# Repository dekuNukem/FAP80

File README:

This repo is still under construction, more information will be available as I continue to add to the documentations and clean up the codebase...

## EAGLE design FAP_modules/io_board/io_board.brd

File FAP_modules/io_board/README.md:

FAP80 I/O Board

This is the I/O board that takes care of Z80 port I/O and interrupts. An EPM570 CPLD replaces 2 dozens of 74 series chips, and a STM32F051C8T6 take on the role of Port and Interrupt controller.

## Overview

* EPM570 CPLD glue logic
* STM32 IO/interrupt controller
* all interrupt modes supported
* 16 ports
* RTC
* UARTs
* Timers
* SD card
* I2C EEPROM
* PS/2 Keyboard
* ESP8266 Header

## Design details

Please see this detailed write-up about the design of this board: [click here](https://dekunukem.wordpress.com/2016/12/25/fap-rebord-the-new-io-card/)

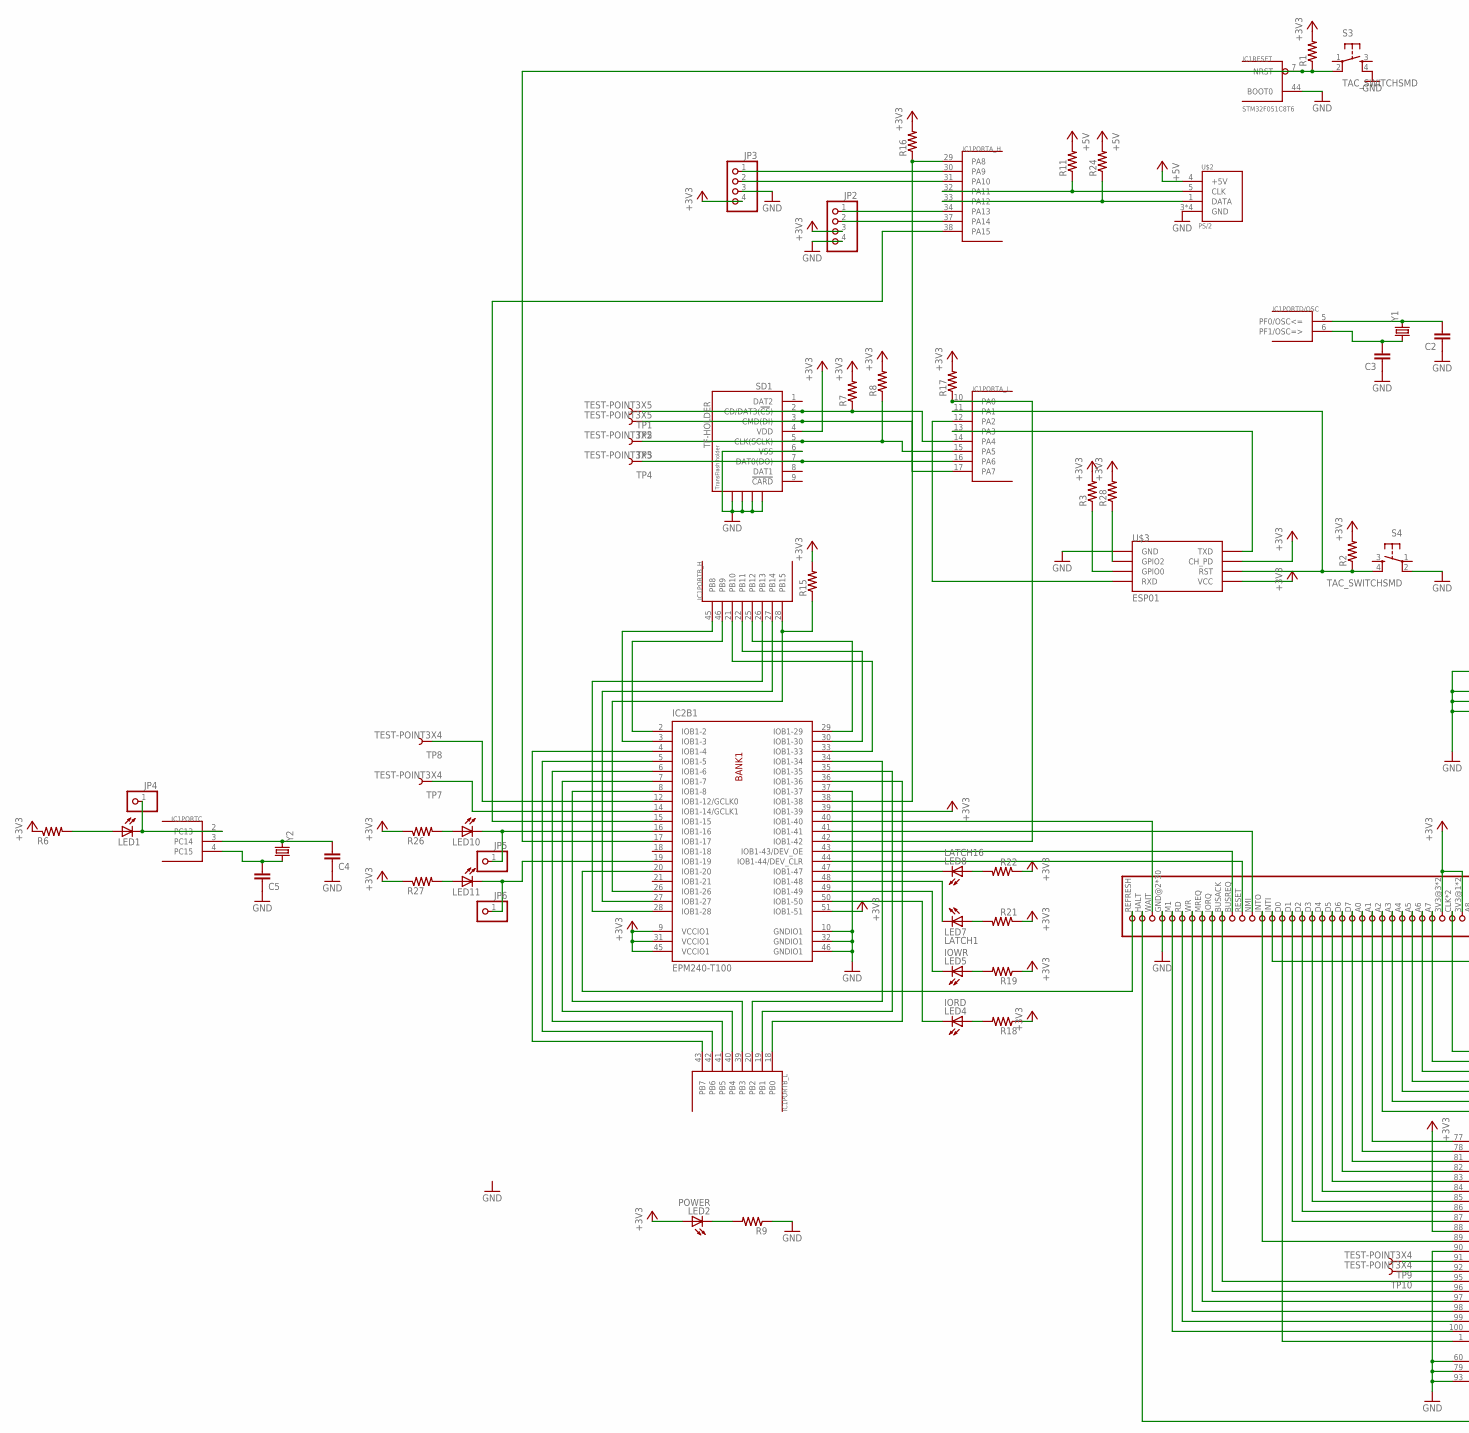
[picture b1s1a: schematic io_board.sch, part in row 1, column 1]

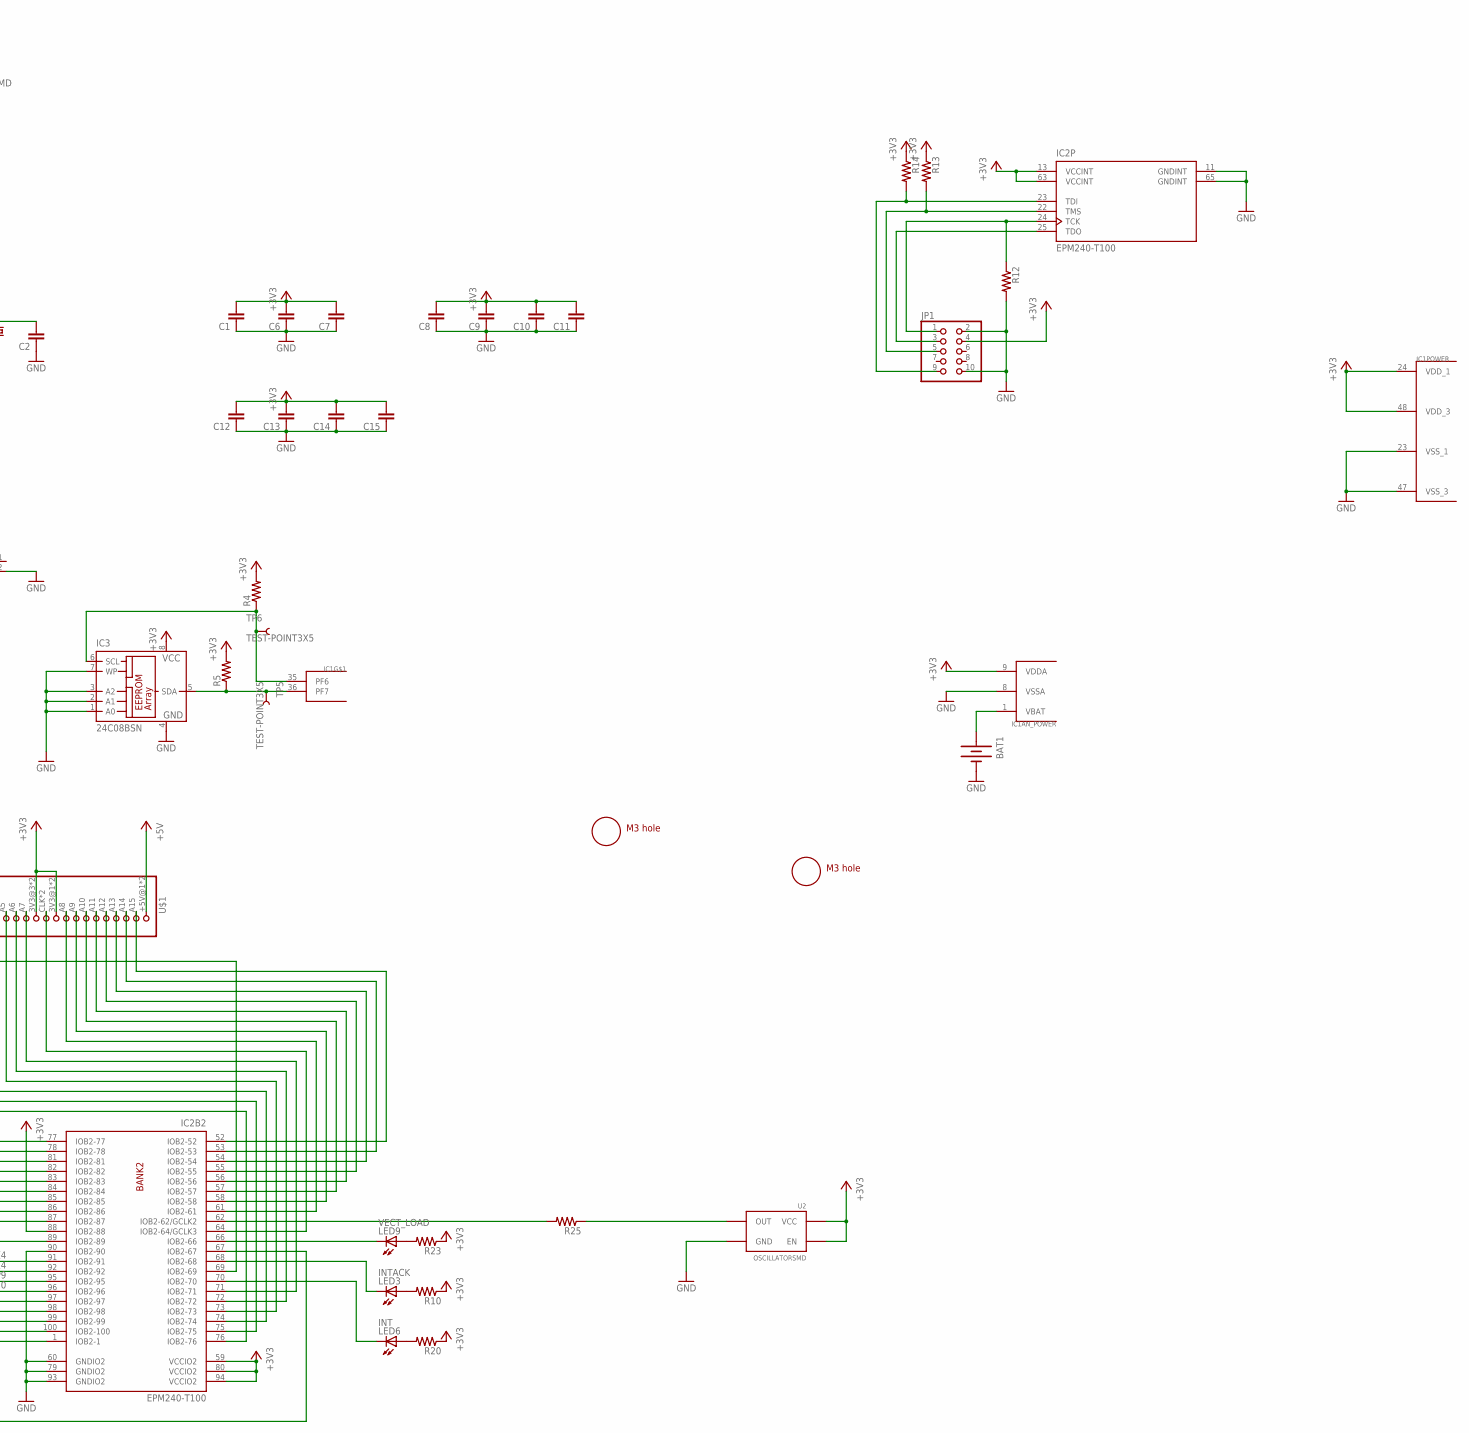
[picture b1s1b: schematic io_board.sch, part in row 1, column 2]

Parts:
BAT1: BATTERY20PTH; BATTCOM_20MM_PTH
C1, C2, C3, C4, C5, C6, C7, C8, C9, C10, C11, C12, C13, C14, C15: CAP0805; 0805
IC1: STM32F051C8T6; TQFP48
IC2: EPM240-T100; TQFP100
IC3: 24C08BSN; SO-08
JP1: PINHD-2X5; 2X05
JP2, JP3: PINHD-1X4/90; 1X04/90
JP4, JP5, JP6: PINHD-1X1; 1X01
LED1, LED10, LED11: LEDCHIP-LED0805; CHIP-LED0805
LED2: POWER; CHIPLED_0805
LED3: INTACK; CHIP-LED0805
LED4: IORD; CHIP-LED0805
LED5: IOWR; CHIP-LED0805
LED6: INT; CHIP-LED0805
LED7: LATCH1; CHIP-LED0805
LED8: LATCH16; CHIP-LED0805
LED9: VECT_LOAD; CHIP-LED0805
R1, R2, R3, R4, R5, R6, R7, R8, R9, R10, R11, R12, R13, R14, R15, R16, R17, R18, R19, R20, R21, R22, R23, R24, R25, R26, R27, R28: RESISTOR0805-RES; 0805
S3, S4: TAC_SWITCHSMD; TACTILE-SWITCH-SMD
SD1: TF-HOLDER; TF-PULL
TP1, TP2, TP3, TP4, TP5, TP6: TEST-POINT3X5; PAD.03X.05
TP7, TP8, TP9, TP10: TEST-POINT3X4; PAD.03X.04
U2: OSCILLATORSMD; CRYSTAL-SMD-7X5
U$1: FAP_BUS; 2X38
U$2: PS/2
U$3: ESP01
U$4, U$5: M3_MOUNTING_HOLE; M3_MOUNTING_HOLE_PACK
Y1: CRYSTALHC49US; HC49US
Y2: CRYSTALTC26H_EZ; TC26HEZ

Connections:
+3V3: C1.2, C6.2, C7.2, C8.2, C9.2, C10.2, C11.2, C12.2, C13.2, C14.2, C15.2, IC1.9 (VDDA), IC1.24 (VDD_1), IC1.48 (VDD_3), IC2.9 (VCCIO1), IC2.13 (VCCINT), IC2.31 (VCCIO1), IC2.39 (IOB1-39), IC2.45 (VCCIO1), IC2.51 (IOB1-51), IC2.59 (VCCIO2), IC2.63 (VCCINT), IC2.80 (VCCIO2), IC2.88 (IOB2-88), IC2.94 (VCCIO2), IC3.8 (VCC), JP1.4, JP2.3, JP3.4, LED2.A, R1.2, R2.2, R3.2, R4.2, R5.2, R6.1, R7.2, R8.2, R10.1, R13.1, R14.1, R15.2, R16.2, R17.2, R18.1, R19.1, R20.1, R21.1, R22.1, R23.1, R26.1, R27.1, R28.2, SD1.4 (VDD), U2.P$1 (EN), U2.P$4 (VCC), U$1.3V3@1 (10), U$1.3V3@2 (10), U$1.3V3@3 (12), U$1.3V3@4 (12), U$3.CH_PD, U$3.VCC
+5V: R11.2, R24.2, U$1.+5V@1 (1), U$1.+5V@2 (1), U$2.4 (+5V)
GND: BAT1.2 (-), C1.1, C2.1, C3.1, C4.1, C5.1, C6.1, C7.1, C8.1, C9.1, C10.1, C11.1, C12.1, C13.1, C14.1, C15.1, IC1.8 (VSSA), IC1.23 (VSS_1), IC1.44 (BOOT0), IC1.47 (VSS_3), IC2.10 (GNDIO1), IC2.11 (GNDINT), IC2.32 (GNDIO1), IC2.37 (IOB1-37), IC2.46 (GNDIO1), IC2.60 (GNDIO2), IC2.65 (GNDINT), IC2.79 (GNDIO2), IC2.90 (IOB2-90), IC2.93 (GNDIO2), IC3.1 (A0), IC3.2 (A1), IC3.3 (A2), IC3.4 (GND), IC3.7 (WP), JP1.2, JP1.10, JP2.4, JP3.3, R9.1, R12.2, S3.4, S4.2, SD1.6 (VSS), SD1.S1, SD1.S2, SD1.S3, SD1.S4, U2.P$2 (GND), U$1.GND@2 (GND), U$1.GND@3 (GND), U$1.GND@4 (GND), U$1.GND@5 (GND), U$1.GND@6 (GND), U$1.GND@7 (GND), U$1.GND@8 (GND), U$1.GND@9 (GND), U$1.GND@13 (GND), U$1.GND@14 (GND), U$1.GND@15 (GND), U$1.GND@16 (GND), U$1.GND@17 (GND), U$1.GND@18 (GND), U$1.GND@19 (GND), U$1.GND@20 (GND), U$1.GND@21 (GND), U$1.GND@22 (GND), U$1.GND@23 (GND), U$1.GND@24 (GND), U$1.GND@25 (GND), U$1.GND@26 (GND), U$1.GND@27 (GND), U$1.GND@28 (GND), U$1.GND@30 (GND), U$1.GND@34 (GND), U$1.GND@35 (GND), U$1.GND@36 (GND), U$1.GND@37 (GND), U$1.GND@38 (GND), U$2.3 (GND), U$2.P$1 (GND), U$2.P$2 (GND), U$2.P$3 (GND), U$3.GND
unnamed: IC2.67 (IOB2-67), U$1.HALT (41)
unnamed: R25.1, U2.P$3 (OUT)
unnamed: IC2.20 (IOB1-20), U$1.REFRESH (42)
unnamed: IC2.12 (IOB1-12/GCLK0), TP8.P$1
unnamed: IC1.7 (NRST), IC2.17 (IOB1-17), R1.1, S3.2
unnamed: C2.2, IC1.5 (PF0/OSC<=), Y1.2
unnamed: C3.2, IC1.6 (PF1/OSC=>), Y1.1
unnamed: C4.2, IC1.3 (PC14), Y2.2
unnamed: C5.2, IC1.4 (PC15), Y2.1
unnamed: BAT1.1 (+), IC1.1 (VBAT)
unnamed: IC1.37 (PA14), JP2.2
unnamed: IC1.34 (PA13), JP2.1
unnamed: IC2.62 (IOB2-62/GCLK2), R25.2
unnamed: IC2.43 (IOB1-43/DEV_OE), U$1.BUSREQ (32)
unnamed: IC2.100 (IOB2-100), U$1.M1 (38)
unnamed: IC2.99 (IOB2-99), U$1.RD (37)
unnamed: IC2.98 (IOB2-98), U$1.WR (36)
unnamed: IC2.97 (IOB2-97), U$1.MREQ (35)
unnamed: IC2.96 (IOB2-96), U$1.IORQ (34)
unnamed: IC2.95 (IOB2-95), U$1.BUSACK (33)
unnamed: IC2.44 (IOB1-44/DEV_CLR), U$1.RESET (31)
unnamed: LED3.A, R10.2
unnamed: IC2.89 (IOB2-89), U$1.INTO (39)
unnamed: IC2.1 (IOB2-1), U$1.D0 (28)
unnamed: IC2.87 (IOB2-87), U$1.D1 (27)
unnamed: IC2.86 (IOB2-86), U$1.D2 (26)
unnamed: IC2.85 (IOB2-85), U$1.D3 (25)
unnamed: IC2.84 (IOB2-84), U$1.D4 (24)
unnamed: IC2.83 (IOB2-83), U$1.D5 (23)
unnamed: IC2.82 (IOB2-82), U$1.D6 (22)
unnamed: IC2.81 (IOB2-81), U$1.D7 (21)
unnamed: IC2.78 (IOB2-78), U$1.A0 (20)
unnamed: IC2.77 (IOB2-77), U$1.A1 (19)
unnamed: IC2.76 (IOB2-76), U$1.A2 (18)
unnamed: IC2.75 (IOB2-75), U$1.A3 (17)
unnamed: IC2.74 (IOB2-74), U$1.A4 (16)
unnamed: IC2.73 (IOB2-73), U$1.A5 (15)
unnamed: IC2.72 (IOB2-72), U$1.A6 (14)
unnamed: IC2.71 (IOB2-71), U$1.A7 (13)
unnamed: IC2.64 (IOB2-64/GCLK3), U$1.CLK (11), U$1.CLK@2 (11)
unnamed: IC2.61 (IOB2-61), U$1.A8 (9)
unnamed: IC2.58 (IOB2-58), U$1.A9 (8)
unnamed: IC2.57 (IOB2-57), U$1.A10 (7)
unnamed: IC2.56 (IOB2-56), U$1.A11 (6)
unnamed: IC2.55 (IOB2-55), U$1.A12 (5)
unnamed: IC2.54 (IOB2-54), U$1.A13 (4)
unnamed: IC2.53 (IOB2-53), U$1.A14 (3)
unnamed: IC2.52 (IOB2-52), U$1.A15 (2)
unnamed: IC1.46 (PB9), IC2.2 (IOB1-2)
unnamed: IC1.45 (PB8), IC2.3 (IOB1-3)
unnamed: IC1.43 (PB7), IC2.4 (IOB1-4)
unnamed: IC1.42 (PB6), IC2.5 (IOB1-5)
unnamed: IC1.41 (PB5), IC2.6 (IOB1-6)
unnamed: IC1.40 (PB4), IC2.7 (IOB1-7)
unnamed: IC1.39 (PB3), IC2.8 (IOB1-8)
unnamed: IC1.28 (PB15), IC2.26 (IOB1-26), R15.1
unnamed: IC1.27 (PB14), IC2.27 (IOB1-27)
unnamed: IC1.26 (PB13), IC2.28 (IOB1-28)
unnamed: IC1.25 (PB12), IC2.29 (IOB1-29)
unnamed: IC1.22 (PB11), IC2.30 (IOB1-30)
unnamed: IC1.21 (PB10), IC2.33 (IOB1-33)
unnamed: IC1.20 (PB2), IC2.34 (IOB1-34)
unnamed: IC1.19 (PB1), IC2.35 (IOB1-35)
unnamed: IC1.18 (PB0), IC2.36 (IOB1-36)
unnamed: IC1.32 (PA11), R11.1, U$2.5 (CLK)
unnamed: IC1.33 (PA12), R24.1, U$2.1 (DATA)
unnamed: IC1.11 (PA1), R2.1, S4.4, U$3.RST
unnamed: R3.1, U$3.GPIO0
unnamed: IC1.36 (PF7), IC3.5 (SDA), R5.1, TP5.P$1
unnamed: IC1.35 (PF6), IC3.6 (SCL), R4.1, TP6.P$1
unnamed: IC1.31 (PA10), JP3.2
unnamed: IC1.30 (PA9), JP3.1
unnamed: IC1.2 (PC13), JP4.1, LED1.C
unnamed: LED1.A, R6.2
unnamed: IC1.12 (PA2), U$3.RX (RXD)
unnamed: IC1.13 (PA3), U$3.TX (TXD)
unnamed: LED4.A, R18.2
unnamed: IC1.14 (PA4), R7.1, SD1.2 (CD/DAT3(!CS!)), TP1.P$1
unnamed: IC1.17 (PA7), SD1.3 (CMD(DI)), TP2.P$1
unnamed: IC1.16 (PA6), SD1.7 (DAT0(DO)), TP4.P$1
unnamed: IC1.15 (PA5), R8.1, SD1.5 (CLK(SCLK)), TP3.P$1
unnamed: LED2.C, R9.2
unnamed: LED7.A, R21.2
unnamed: LED5.A, R19.2
unnamed: IC1.38 (PA15), IC2.15 (IOB1-15)
unnamed: IC1.10 (PA0), IC2.42 (IOB1-42), R17.1
unnamed: IC1.29 (PA8), IC2.38 (IOB1-38), R16.1
unnamed: LED6.A, R20.2
unnamed: LED8.A, R22.2
unnamed: IC2.47 (IOB1-47), LED8.C
unnamed: IC2.48 (IOB1-48), LED7.C
unnamed: IC2.49 (IOB1-49), LED5.C
unnamed: IC2.50 (IOB1-50), LED4.C
unnamed: LED9.A, R23.2
unnamed: IC2.66 (IOB2-66), LED9.C
unnamed: IC2.68 (IOB2-68), LED3.C
unnamed: IC2.70 (IOB2-70), LED6.C
unnamed: IC2.14 (IOB1-14/GCLK1), TP7.P$1
unnamed: IC2.69 (IOB2-69), U$1.INTI (29)
unnamed: IC2.41 (IOB1-41), U$1.NMI (30)
unnamed: IC2.40 (IOB1-40), U$1.WAIT (40)
unnamed: LED10.A, R26.2
unnamed: IC2.16 (IOB1-16), JP5.1, LED10.C
unnamed: LED11.A, R27.2
unnamed: IC2.19 (IOB1-19), JP6.1, LED11.C
unnamed: IC2.91 (IOB2-91), TP9.P$1
unnamed: IC2.92 (IOB2-92), TP10.P$1
unnamed: R28.1, U$3.GPIO2
TCK: IC2.24 (TCK), JP1.1, R12.1
TDI: IC2.23 (TDI), JP1.9, R14.2
TDO: IC2.25 (TDO), JP1.3
TMS: IC2.22 (TMS), JP1.5, R13.2

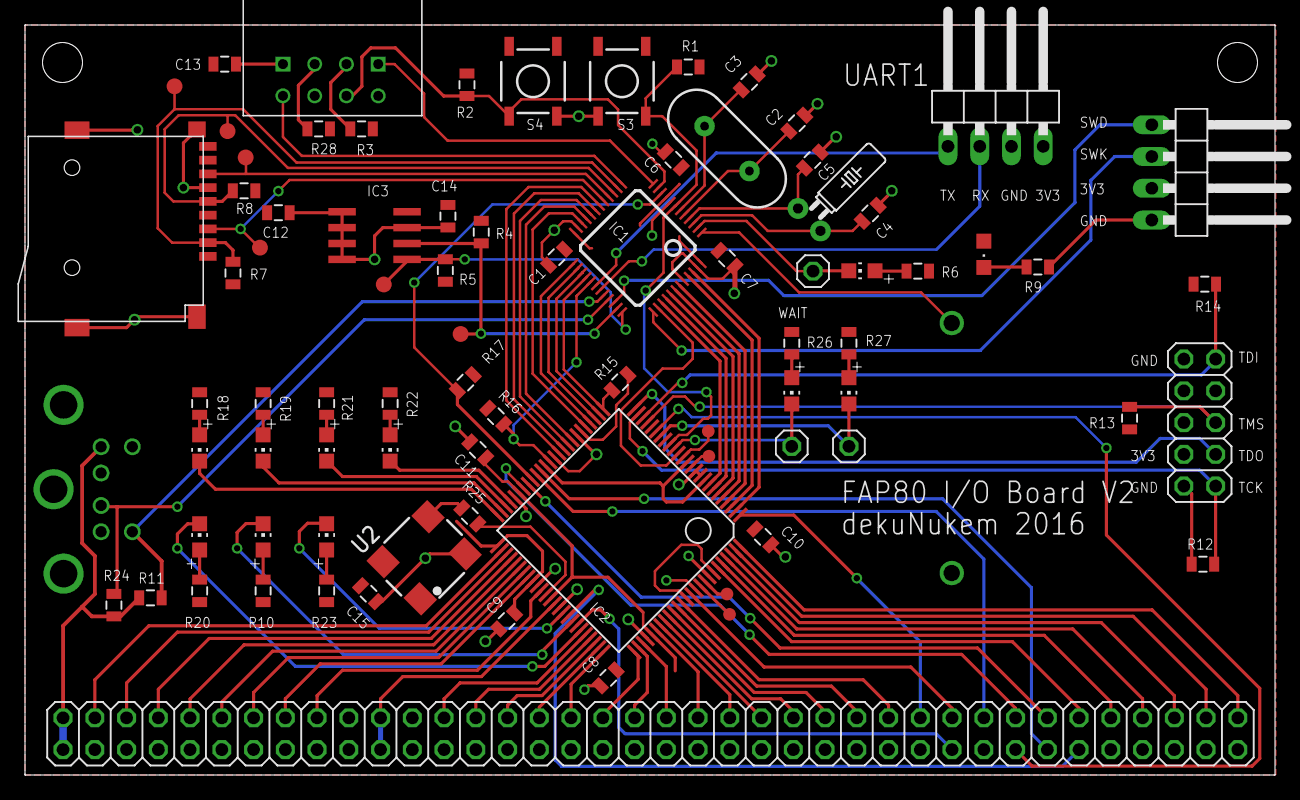
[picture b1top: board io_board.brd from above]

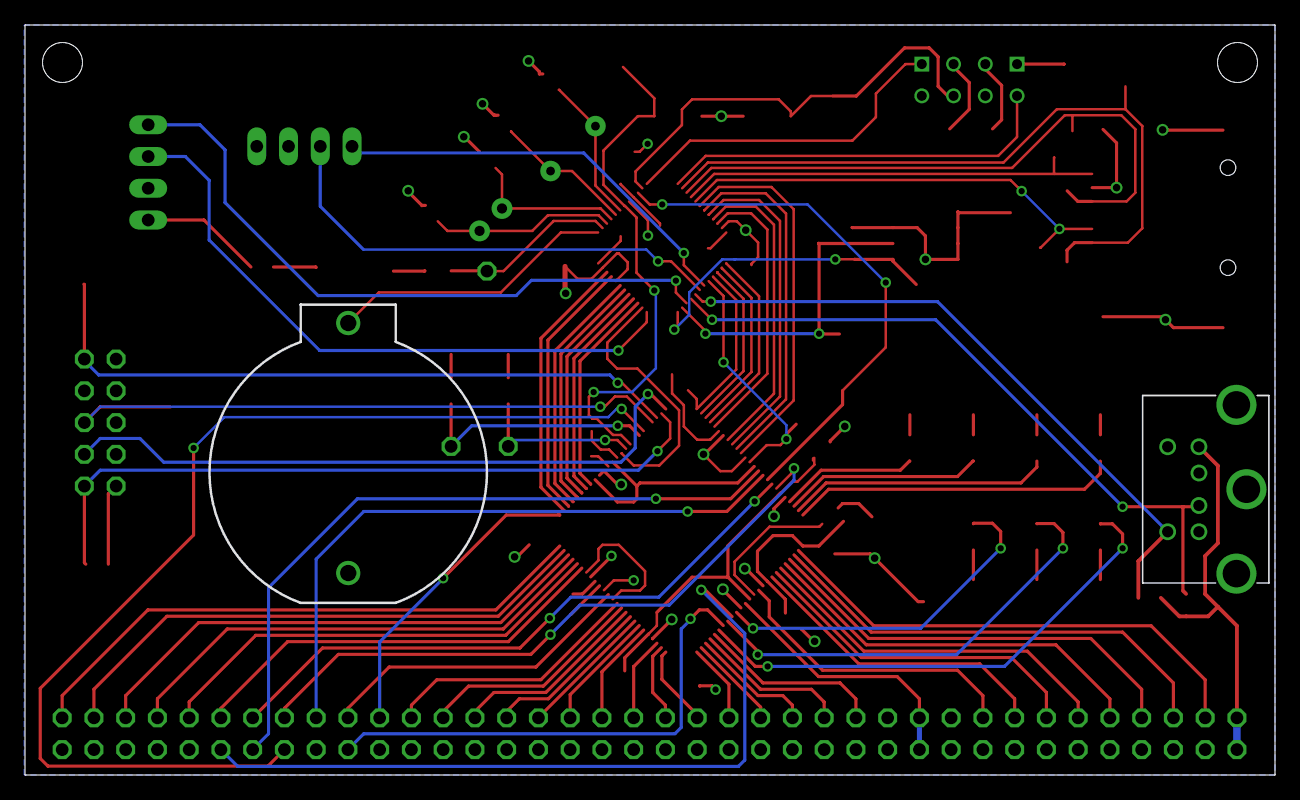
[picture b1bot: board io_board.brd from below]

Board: 2 copper layers, 100.0 x 60.0 mm, 85 parts (2 on the bottom side), 115 nets.

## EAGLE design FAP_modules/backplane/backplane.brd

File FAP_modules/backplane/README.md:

# FAP80 active backplane

The backbone of FAP80, all the modules plug into it. The backplane has 5 slots, each 2cm apart, a STM32F072RBT6, a 2.2 inch serial LCD for displaying execution status, and 6 buttons for controlling the computer.

The entire bus is connected to the STM32, which drives the Z80 clock through one of its PWM channels, the uC also monitors the bus content and display it on a LCD. It can also kick the Z80 off the bus and read/write ROM/RAM directly. The backplane communicates with a PC via USB, which also powers the FAP80.

## Usage

When powered on, the backplane resets the Z80 then stops. Press RUN/STOP button to start FAP80 execution at full speed, press CLK STEP for single clock step, press INS STEP for single instruction step(which takes variable numbers of clock cycles depending on the instruction), press Z80 RESET to reset the Z80, and MCU RESET to reset the backplane itself. TRACE button currently doesn't do anything, I'll implement trace function when I need it.

The backplane will appear as a USB serial device when plugged into a computer. send `epm` to enter program mode. Once entered, you can send `r address` to read a memory address, `w address value` to write to a memory address, and `z` to erase entire ROM to 0xff. Send `qpm` to quit program mode. Note all numerical arguments are in decimal, and all commands ends in `\r\n`.

## Bus connector

Each connector is a 38x2 double row female pin header, pinout below.
I used 2 rows to give more grip to modules that has been plugged in, as well as improving noise immunity.  All Z80 signals are available on the bus.

Interrupt chaining is supported. INTI is the interrupt input, while INTO is interrupt output. The board closest to the Z80 CPU board has the highest interrupt priority.

|     |        | 
|-----|--------| 
| GND | M1     | 
| GND | RD     | 
| GND | WR     | 
| GND | MREQ   | 
| GND | IORQ   | 
| HALT | BUACK  | 
| WAIT | BUSREQ | 
| REFRESH | RESET  | 
| GND | NMI    | 
| INTI | INTO    | 
| GND | D0     | 
| GND | D1     | 
| GND | D2     | 
| GND | D3     | 
| GND | D4     | 
| GND | D5     | 
| GND | D6     | 
| GND | D7     | 
| GND | A0     | 
| GND | A1     | 
| GND | A2     | 
| GND | A3     | 
| GND | A4     | 
| GND | A5     | 
| GND | A6     | 
| GND | A7     | 
| 3V3 | 3V3    | 
| CLK | CLK    | 
| 3V3 | 3V3    | 
| GND | A8     | 
| GND | A9     | 
| GND | A10    | 
| GND | A11    | 
| GND | A12    | 
| GND | A13    | 
| GND | A14    | 
| GND | A15    | 
| 5V  | 5V     | 

## LCD

I used a LCD from [Nextion](https://www.itead.cc/wiki/Nextion_HMI_Solution), they make a whole range of LCDs in different sizes, some with resistive touch screen. The neat thing is that they are controlled by standard serial, so it's much easier to use than I2C or SPI LCDs. And apparently it has a companion software on PC where you can design an entire UI and upload it into the LCD. For this project I didn't bother with any of that since it just displays some text strings. I used their smallest and cheapest one. The serial commands for it can be found [here](https://www.itead.cc/wiki/Nextion_Instruction_Set), the only two I used is CLS (clear screen) and XSTR(print string).

## Blog entries

For details about the old backplane, see [here](https://dekunukem.wordpress.com/2016/02/21/part-1-bus-board-cpu-board-and-freerunning-fap/)

For a brief introduction of the new backplane, see [here](https://dekunukem.wordpress.com/2016/12/22/fap-reborn-backplane/)

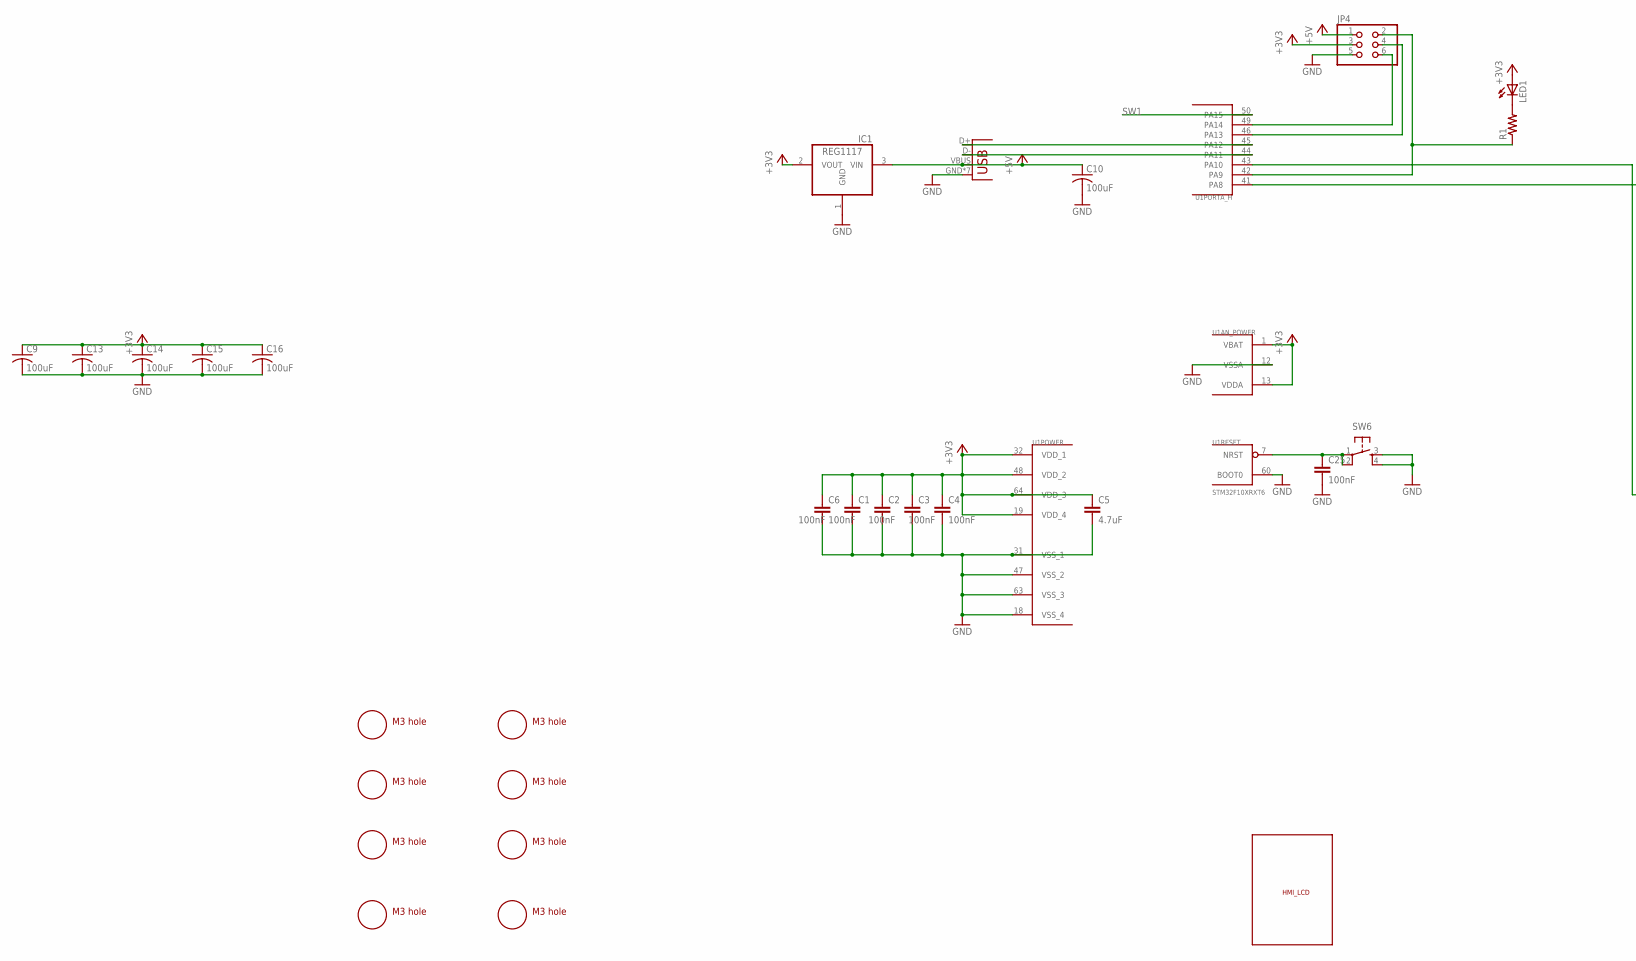
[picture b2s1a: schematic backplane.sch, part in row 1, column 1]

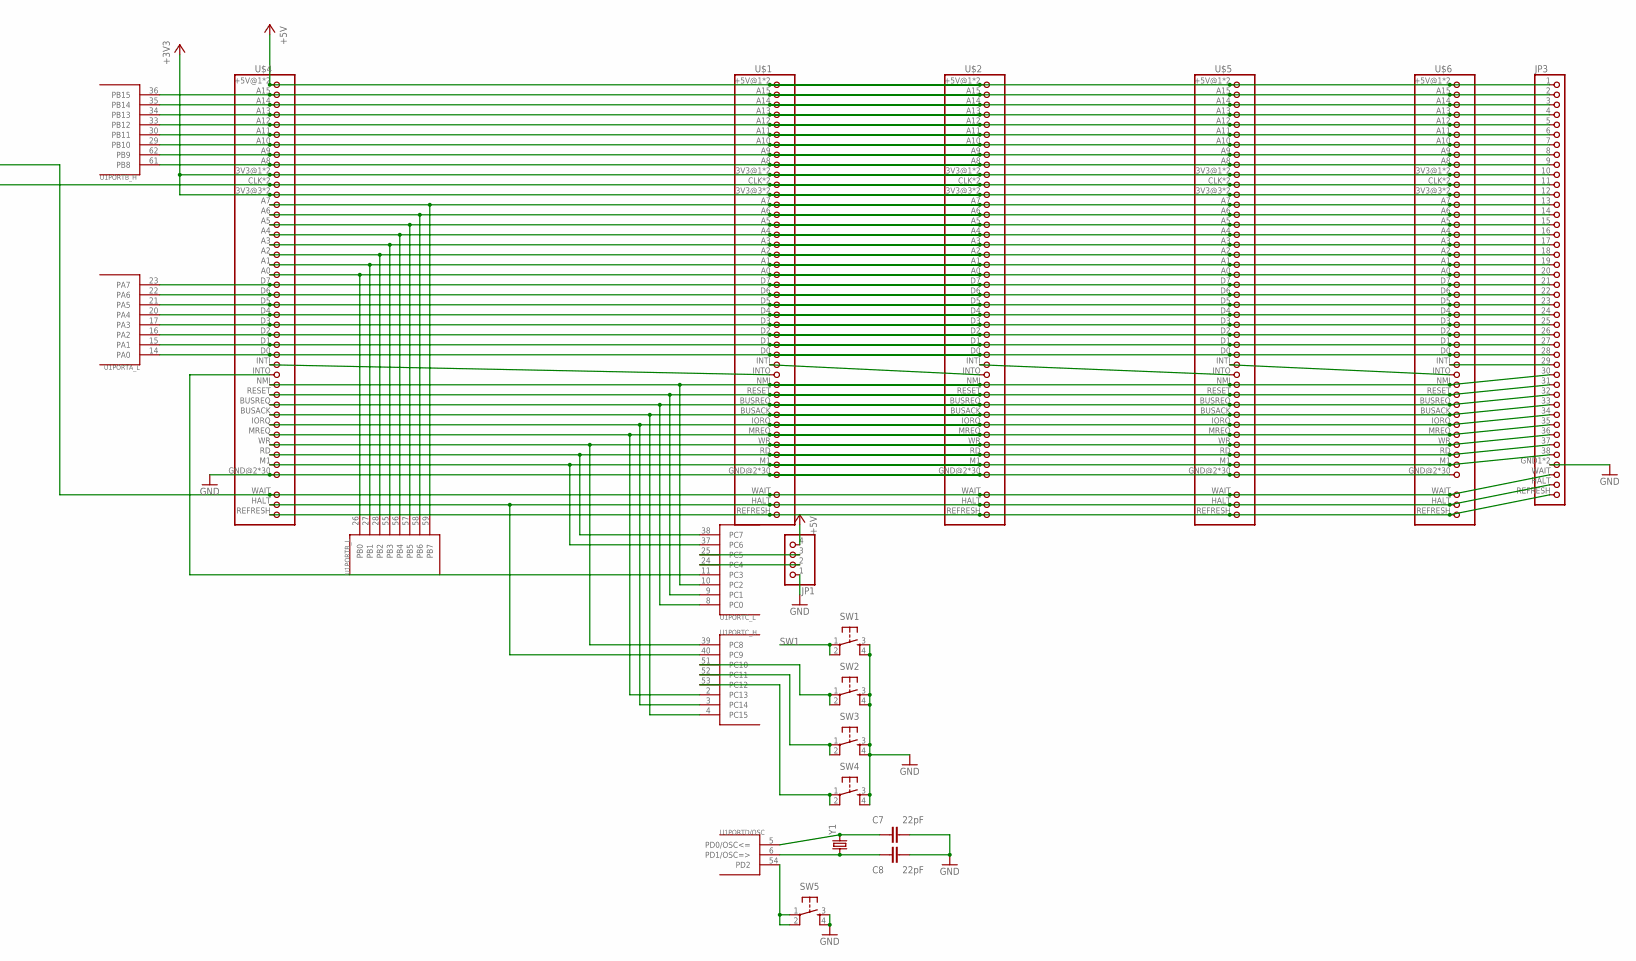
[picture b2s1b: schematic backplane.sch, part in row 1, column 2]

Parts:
C1, C2, C3, C4, C6, C25: 100nF; 0805
C5: 4.7uF; 0805
C7, C8: 22pF; 0805
C9, C10, C13, C14, C15, C16: 100uF; C1210
IC1: REG1117; SOT223
J1: USB-MICROB
JP1: PINHD-1X4; 1X04
JP3: PINHD-1X38; 1X38
JP4: PINHD-2X3; 2X03
LED1: LEDCHIP-LED0805; CHIP-LED0805
R1: R-US_R0805; R0805
SW1, SW2, SW3, SW4, SW5, SW6: SWITCH_SPST_4_PINSQUARE; TACTILE-SWITCH-SMD
U1: STM32F10XRXT6; TQFP64
U$1, U$2, U$4, U$5, U$6: FAP_BUS; 2X38
U$3: HMI_LCD
U$7, U$8, U$9, U$10, U$11, U$12, U$13, U$14: M3_MOUNTING_HOLE; M3_MOUNTING_HOLE_PACK
Y1: CRYSTALHC49US; HC49US

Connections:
+3V3: C1.1, C2.1, C3.1, C4.1, C5.1, C6.1, C9.1, C13.1, C14.1, C15.1, C16.1, IC1.2 (VOUT), JP3.10, JP3.12, JP4.3, LED1.A, U1.1 (VBAT), U1.13 (VDDA), U1.19 (VDD_4), U1.32 (VDD_1), U1.48 (VDD_2), U1.64 (VDD_3), U$1.3V3@1 (10), U$1.3V3@2 (10), U$1.3V3@3 (12), U$1.3V3@4 (12), U$2.3V3@1 (10), U$2.3V3@2 (10), U$2.3V3@3 (12), U$2.3V3@4 (12), U$4.3V3@1 (10), U$4.3V3@2 (10), U$4.3V3@3 (12), U$4.3V3@4 (12), U$5.3V3@1 (10), U$5.3V3@2 (10), U$5.3V3@3 (12), U$5.3V3@4 (12), U$6.3V3@1 (10), U$6.3V3@2 (10), U$6.3V3@3 (12), U$6.3V3@4 (12)
+5V: C10.1, IC1.3 (VIN), J1.VBUS, JP1.4, JP3.1, JP4.1, U$1.+5V@1 (1), U$1.+5V@2 (1), U$2.+5V@1 (1), U$2.+5V@2 (1), U$4.+5V@1 (1), U$4.+5V@2 (1), U$5.+5V@1 (1), U$5.+5V@2 (1), U$6.+5V@1 (1), U$6.+5V@2 (1)
A0: JP3.20, U1.26 (PB0), U$1.A0 (20), U$2.A0 (20), U$4.A0 (20), U$5.A0 (20), U$6.A0 (20)
A7: JP3.13, U1.59 (PB7), U$1.A7 (13), U$2.A7 (13), U$4.A7 (13), U$5.A7 (13), U$6.A7 (13)
GND: C1.2, C2.2, C3.2, C4.2, C5.2, C6.2, C7.2, C8.2, C9.2, C10.2, C13.2, C14.2, C15.2, C16.2, C25.2, IC1.1 (GND), J1.GND, J1.P1 (GND), J1.P2 (GND), J1.P3 (GND), J1.P4 (GND), J1.P5 (GND), J1.P6 (GND), JP1.1, JP3.GND1 (GND), JP3.GND2 (GND), JP4.5, SW1.3, SW1.4, SW2.3, SW2.4, SW3.3, SW3.4, SW4.3, SW4.4, SW5.3, SW5.4, SW6.3, SW6.4, U1.12 (VSSA), U1.18 (VSS_4), U1.31 (VSS_1), U1.47 (VSS_2), U1.60 (BOOT0), U1.63 (VSS_3), U$1.GND@2 (GND), U$1.GND@3 (GND), U$1.GND@4 (GND), U$1.GND@5 (GND), U$1.GND@6 (GND), U$1.GND@7 (GND), U$1.GND@8 (GND), U$1.GND@9 (GND), U$1.GND@13 (GND), U$1.GND@14 (GND), U$1.GND@15 (GND), U$1.GND@16 (GND), U$1.GND@17 (GND), U$1.GND@18 (GND), U$1.GND@19 (GND), U$1.GND@20 (GND), U$1.GND@21 (GND), U$1.GND@22 (GND), U$1.GND@23 (GND), U$1.GND@24 (GND), U$1.GND@25 (GND), U$1.GND@26 (GND), U$1.GND@27 (GND), U$1.GND@28 (GND), U$1.GND@30 (GND), U$1.GND@34 (GND), U$1.GND@35 (GND), U$1.GND@36 (GND), U$1.GND@37 (GND), U$1.GND@38 (GND), U$2.GND@2 (GND), U$2.GND@3 (GND), U$2.GND@4 (GND), U$2.GND@5 (GND), U$2.GND@6 (GND), U$2.GND@7 (GND), U$2.GND@8 (GND), U$2.GND@9 (GND), U$2.GND@13 (GND), U$2.GND@14 (GND), U$2.GND@15 (GND), U$2.GND@16 (GND), U$2.GND@17 (GND), U$2.GND@18 (GND), U$2.GND@19 (GND), U$2.GND@20 (GND), U$2.GND@21 (GND), U$2.GND@22 (GND), U$2.GND@23 (GND), U$2.GND@24 (GND), U$2.GND@25 (GND), U$2.GND@26 (GND), U$2.GND@27 (GND), U$2.GND@28 (GND), U$2.GND@30 (GND), U$2.GND@34 (GND), U$2.GND@35 (GND), U$2.GND@36 (GND), U$2.GND@37 (GND), U$2.GND@38 (GND), U$4.GND@2 (GND), U$4.GND@3 (GND), U$4.GND@4 (GND), U$4.GND@5 (GND), U$4.GND@6 (GND), U$4.GND@7 (GND), U$4.GND@8 (GND), U$4.GND@9 (GND), U$4.GND@13 (GND), U$4.GND@14 (GND), U$4.GND@15 (GND), U$4.GND@16 (GND), U$4.GND@17 (GND), U$4.GND@18 (GND), U$4.GND@19 (GND), U$4.GND@20 (GND), U$4.GND@21 (GND), U$4.GND@22 (GND), U$4.GND@23 (GND), U$4.GND@24 (GND), U$4.GND@25 (GND), U$4.GND@26 (GND), U$4.GND@27 (GND), U$4.GND@28 (GND), U$4.GND@30 (GND), U$4.GND@34 (GND), U$4.GND@35 (GND), U$4.GND@36 (GND), U$4.GND@37 (GND), U$4.GND@38 (GND), U$5.GND@2 (GND), U$5.GND@3 (GND), U$5.GND@4 (GND), U$5.GND@5 (GND), U$5.GND@6 (GND), U$5.GND@7 (GND), U$5.GND@8 (GND), U$5.GND@9 (GND), U$5.GND@13 (GND), U$5.GND@14 (GND), U$5.GND@15 (GND), U$5.GND@16 (GND), U$5.GND@17 (GND), U$5.GND@18 (GND), U$5.GND@19 (GND), U$5.GND@20 (GND), U$5.GND@21 (GND), U$5.GND@22 (GND), U$5.GND@23 (GND), U$5.GND@24 (GND), U$5.GND@25 (GND), U$5.GND@26 (GND), U$5.GND@27 (GND), U$5.GND@28 (GND), U$5.GND@30 (GND), U$5.GND@34 (GND), U$5.GND@35 (GND), U$5.GND@36 (GND), U$5.GND@37 (GND), U$5.GND@38 (GND), U$6.GND@2 (GND), U$6.GND@3 (GND), U$6.GND@4 (GND), U$6.GND@5 (GND), U$6.GND@6 (GND), U$6.GND@7 (GND), U$6.GND@8 (GND), U$6.GND@9 (GND), U$6.GND@13 (GND), U$6.GND@14 (GND), U$6.GND@15 (GND), U$6.GND@16 (GND), U$6.GND@17 (GND), U$6.GND@18 (GND), U$6.GND@19 (GND), U$6.GND@20 (GND), U$6.GND@21 (GND), U$6.GND@22 (GND), U$6.GND@23 (GND), U$6.GND@24 (GND), U$6.GND@25 (GND), U$6.GND@26 (GND), U$6.GND@27 (GND), U$6.GND@28 (GND), U$6.GND@30 (GND), U$6.GND@34 (GND), U$6.GND@35 (GND), U$6.GND@36 (GND), U$6.GND@37 (GND), U$6.GND@38 (GND)
unnamed: JP3.29, U$6.INTI (29)
unnamed: U$5.INTI (29), U$6.INTO (39)
unnamed: JP3.3, U1.35 (PB14), U$1.A14 (3), U$2.A14 (3), U$4.A14 (3), U$5.A14 (3), U$6.A14 (3)
unnamed: JP3.4, U1.34 (PB13), U$1.A13 (4), U$2.A13 (4), U$4.A13 (4), U$5.A13 (4), U$6.A13 (4)
unnamed: U$1.INTO (39), U$4.INTI (29)
unnamed: U$1.INTI (29), U$2.INTO (39)
unnamed: JP3.7, U1.29 (PB10), U$1.A10 (7), U$2.A10 (7), U$4.A10 (7), U$5.A10 (7), U$6.A10 (7)
unnamed: U1.11 (PC3), U$4.INTO (39)
unnamed: JP3.9, U1.61 (PB8), U$1.A8 (9), U$2.A8 (9), U$4.A8 (9), U$5.A8 (9), U$6.A8 (9)
unnamed: U$2.INTI (29), U$5.INTO (39)
unnamed: JP3.22, U1.22 (PA6), U$1.D6 (22), U$2.D6 (22), U$4.D6 (22), U$5.D6 (22), U$6.D6 (22)
unnamed: LED1.C, R1.2
unnamed: JP3.24, U1.20 (PA4), U$1.D4 (24), U$2.D4 (24), U$4.D4 (24), U$5.D4 (24), U$6.D4 (24)
unnamed: JP3.27, U1.15 (PA1), U$1.D1 (27), U$2.D1 (27), U$4.D1 (27), U$5.D1 (27), U$6.D1 (27)
unnamed: JP3.26, U1.16 (PA2), U$1.D2 (26), U$2.D2 (26), U$4.D2 (26), U$5.D2 (26), U$6.D2 (26)
unnamed: JP3.28, U1.14 (PA0), U$1.D0 (28), U$2.D0 (28), U$4.D0 (28), U$5.D0 (28), U$6.D0 (28)
unnamed: JP3.REFRESH, U$1.REFRESH, U$2.REFRESH, U$4.REFRESH, U$5.REFRESH, U$6.REFRESH
unnamed: JP3.30, U1.10 (PC2), U$1.NMI (30), U$2.NMI (30), U$4.NMI (30), U$5.NMI (30), U$6.NMI (30)
unnamed: JP3.HALT, U1.40 (PC9), U$1.HALT, U$2.HALT, U$4.HALT, U$5.HALT, U$6.HALT
unnamed: JP3.25, U1.17 (PA3), U$1.D3 (25), U$2.D3 (25), U$4.D3 (25), U$5.D3 (25), U$6.D3 (25)
unnamed: JP3.31, U1.9 (PC1), U$1.RESET (31), U$2.RESET (31), U$4.RESET (31), U$5.RESET (31), U$6.RESET (31)
unnamed: JP3.32, U1.8 (PC0), U$1.BUSREQ (32), U$2.BUSREQ (32), U$4.BUSREQ (32), U$5.BUSREQ (32), U$6.BUSREQ (32)
unnamed: JP3.35, U1.2 (PC13), U$1.MREQ (35), U$2.MREQ (35), U$4.MREQ (35), U$5.MREQ (35), U$6.MREQ (35)
unnamed: JP3.36, U1.39 (PC8), U$1.WR (36), U$2.WR (36), U$4.WR (36), U$5.WR (36), U$6.WR (36)
unnamed: JP3.WAIT, U1.43 (PA10), U$1.WAIT, U$2.WAIT, U$4.WAIT, U$5.WAIT, U$6.WAIT
unnamed: JP3.38, U1.37 (PC6), U$1.M1 (38), U$2.M1 (38), U$4.M1 (38), U$5.M1 (38), U$6.M1 (38)
unnamed: JP3.23, U1.21 (PA5), U$1.D5 (23), U$2.D5 (23), U$4.D5 (23), U$5.D5 (23), U$6.D5 (23)
unnamed: JP3.15, U1.57 (PB5), U$1.A5 (15), U$2.A5 (15), U$4.A5 (15), U$5.A5 (15), U$6.A5 (15)
unnamed: JP3.8, U1.62 (PB9), U$1.A9 (8), U$2.A9 (8), U$4.A9 (8), U$5.A9 (8), U$6.A9 (8)
unnamed: JP3.21, U1.23 (PA7), U$1.D7 (21), U$2.D7 (21), U$4.D7 (21), U$5.D7 (21), U$6.D7 (21)
unnamed: JP3.6, U1.30 (PB11), U$1.A11 (6), U$2.A11 (6), U$4.A11 (6), U$5.A11 (6), U$6.A11 (6)
unnamed: JP3.5, U1.33 (PB12), U$1.A12 (5), U$2.A12 (5), U$4.A12 (5), U$5.A12 (5), U$6.A12 (5)
unnamed: JP3.2, U1.36 (PB15), U$1.A15 (2), U$2.A15 (2), U$4.A15 (2), U$5.A15 (2), U$6.A15 (2)
unnamed: JP3.19, U1.27 (PB1), U$1.A1 (19), U$2.A1 (19), U$4.A1 (19), U$5.A1 (19), U$6.A1 (19)
unnamed: JP3.17, U1.55 (PB3), U$1.A3 (17), U$2.A3 (17), U$4.A3 (17), U$5.A3 (17), U$6.A3 (17)
unnamed: JP3.16, U1.56 (PB4), U$1.A4 (16), U$2.A4 (16), U$4.A4 (16), U$5.A4 (16), U$6.A4 (16)
unnamed: JP3.11, U1.41 (PA8), U$1.CLK (11), U$1.CLK@2 (11), U$2.CLK (11), U$2.CLK@2 (11), U$4.CLK (11), U$4.CLK@2 (11), U$5.CLK (11), U$5.CLK@2 (11), U$6.CLK (11), U$6.CLK@2 (11)
unnamed: JP1.2, U1.24 (PC4)
unnamed: JP1.3, U1.25 (PC5)
unnamed: JP3.33, U1.4 (PC15), U$1.BUSACK (33), U$2.BUSACK (33), U$4.BUSACK (33), U$5.BUSACK (33), U$6.BUSACK (33)
unnamed: JP3.34, U1.3 (PC14), U$1.IORQ (34), U$2.IORQ (34), U$4.IORQ (34), U$5.IORQ (34), U$6.IORQ (34)
unnamed: C25.1, SW6.1, SW6.2, U1.7 (NRST)
unnamed: SW5.1, SW5.2, U1.54 (PD2)
unnamed: JP4.6, U1.49 (PA14)
unnamed: SW2.1, SW2.2, U1.51 (PC10)
unnamed: SW3.1, SW3.2, U1.52 (PC11)
unnamed: SW4.1, SW4.2, U1.53 (PC12)
unnamed: JP4.4, U1.46 (PA13)
unnamed: JP4.2, R1.1, U1.42 (PA9)
unnamed: JP3.37, U1.38 (PC7), U$1.RD (37), U$2.RD (37), U$4.RD (37), U$5.RD (37), U$6.RD (37)
unnamed: J1.D+, U1.45 (PA12)
unnamed: C8.1, U1.6 (PD1/OSC=>), Y1.1
unnamed: C7.1, U1.5 (PD0/OSC<=), Y1.2
unnamed: J1.D-, U1.44 (PA11)
unnamed: JP3.14, U1.58 (PB6), U$1.A6 (14), U$2.A6 (14), U$4.A6 (14), U$5.A6 (14), U$6.A6 (14)
unnamed: JP3.18, U1.28 (PB2), U$1.A2 (18), U$2.A2 (18), U$4.A2 (18), U$5.A2 (18), U$6.A2 (18)
SW1: SW1.1, SW1.2, U1.50 (PA15)

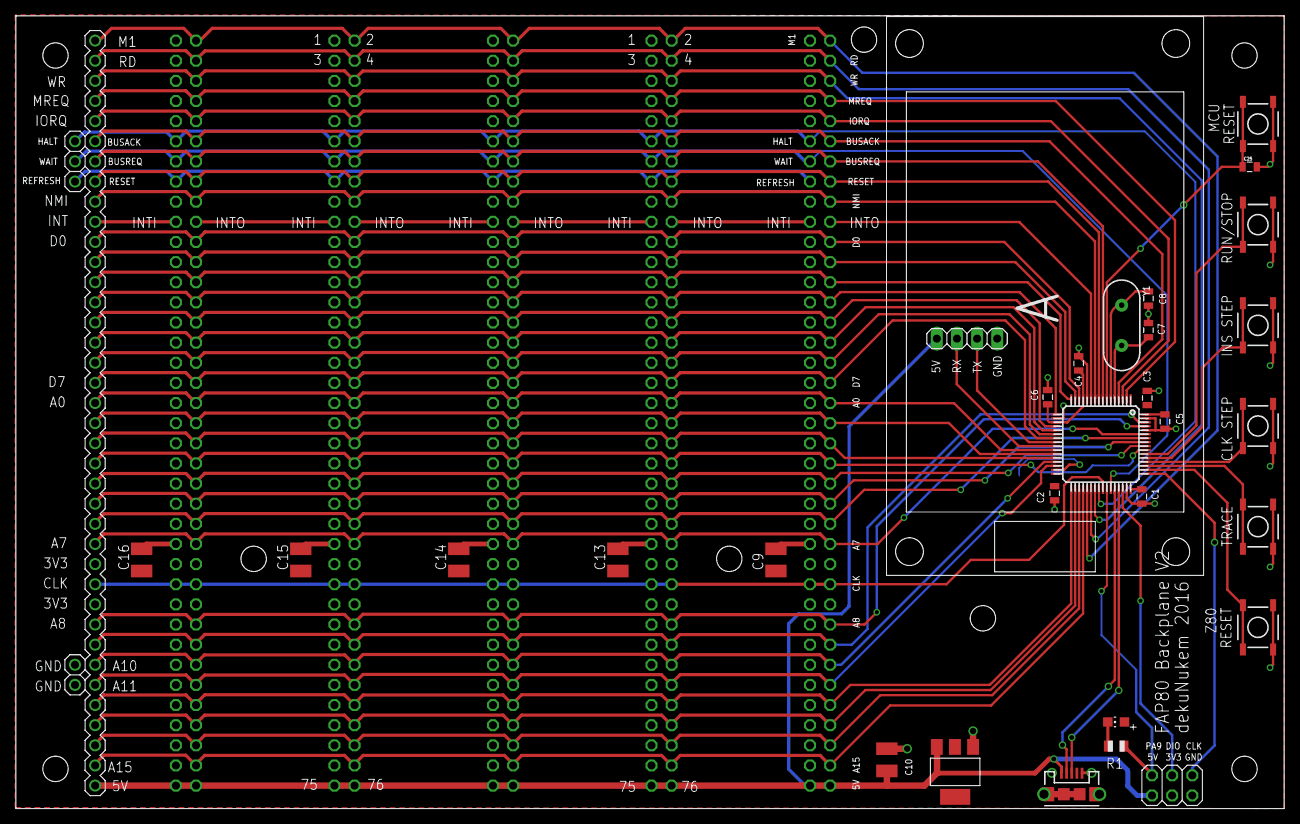
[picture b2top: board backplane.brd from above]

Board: 2 copper layers, 160.0 x 100.0 mm, 44 parts (0 on the bottom side), 62 nets.

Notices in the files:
parts and their libraries:
SparkFun-Electromechanical: Licensing: Creative Commons ShareAlike 4.0 International - https://creativecommons.org/licenses/by-sa/4.0
